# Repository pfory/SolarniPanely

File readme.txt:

Odkazy
http://pavelrichter.net/category/projekty/fotovoltaika/
http://blog.chupasweb.net/archives/494
https://www.youtube.com/watch?v=ouLa4Ftu3O8¨

Popis
Solární panel z jednotlivých solárních článků. Ukládání přebytečné energie do baterie, použít autobaterii, později nahradit něčím lepším. Vyrobenou energii měnit na 230V a napájet spotřebiče

Co potřebuji
- solání články + kabely, ebay 5x5" 125x125mm, 2,7W/článek nominální napětí 0,55 - 0,6V/článek 
https://www.ebay.com/itm/2-8W-125MM-Monocrystalline-Solar-Cells-5x5-A-Grade-For-DIY-Solar-Panels/113344175030?hash=item1a63d6dbb6:m:m1efJgrAq3WPJkaR0fac6-Q:rk:6:pf:0
https://www.ebay.com/itm/40Pcs-125MM-Monocrystalline-Silicon-Solar-Cells-For-DIY-Solar-Panels/302911830537?hash=item4686f3ba09:g:skYAAOSw8hhan8Zm
kolektor 100Wp cca 36ks 9*4 napětí 18V, proud 5,5A 		50ks cena cca 1383,- 
36 článků 996,-

4*125+3*10 =500+30  =530mm   +2*10  +2*19    = 530+20+38 =588mm     590   

9*125+8*1 =1125+8 =1133    +2*10    +2*19    = 1133+20+38=1191mm    1190
                    články  mezera rámeček

rámeček alu profil U 40x25x3 90/m
125+125+62+62=3,75m = 337,-

profil na 2 panely 987 + 140 doprava = 1127
1 panel 560,-

rám 670x1250
sklo 670-2x10=650
1250-2x10=1230

profil pro uchycení na střechu - https://www.ehlinik.cz/al-profil-solar-40x40/pro-2EV0000101.html
délka 2x67 + 2x67 = 4x67 = 268 + mezery 3x2 + kraje 2x5 = 268 + 16 = 284

pro 4 panely zapojené paralelně:
napětí 18V
proud 5,5*4=22A  měl by stačit vodič o průřezu 2,5
výkon 4x100Wp=400Wp

- alu profil https://www.alupa.cz/hlinik/hlinikovy-u-profil-nepr-11x25x13x18/pro-2YS0000101.html 225,-
- sklo 690/m2 panel cca 1m2 - 690,-
- silikon
- regulátor	400,- https://www.ebay.co.uk/itm/10-50A-12-24V-PWM-LCD-Automatic-Solar-Panel-Charger-Controller-Battery-Regulator/122717669692?_trkparms=aid%3D555018%26algo%3DPL.SIM%26ao%3D1%26asc%3D20140122125356%26meid%3Da21eef7c86044d88986fb21765aa5a55%26pid%3D100005%26rk%3D2%26rkt%3D12%26mehot%3Dpp%26sd%3D302957473646%26itm%3D122717669692&_trksid=p2047675.c100005.m1851
- baterie	autobaterie
- měnič 230V
- kabely
- diody
- konektory
- cín
- lepicí páska
- štětec
- nůžky
- ....

Nářadí
- pájka
- svěrák
- pila
- pilník
- šroubovák
- kladivo
- kleště
- klíče

Jeden 100W kolektor by měl za rok vyrobit 80kWh tj. při ceně 6Kč/kWh je cca 480,- za rok

Cenu kolektoru
články 996,-
sklo 782,-
alu profil 350,-
silikon 70,-
tištěné díly + šrouby 50,-

celkem 2248,-

Eko verze s EVA
články 780,-
alu profil 30x20x2 50,7 bez DPH - 3m = 184,-
alu profil 40x20x2 55,9         - 3m = 203,-
doprava 140,-
sklo 4mm cca 115x55 = 380,-
EVA 1000x500*0,4 1m 181,- = 362,-

celkem 780+200+400+362=1742,-

- regulátor 460,-

profil 40x25x3 - 1250
profil 40x25x3 - 620

1.panel
sklo 4mm 65*123
sklo 3mm 65*123
celkem 782,-

2.panel
sklo 4mm 
sklo 3mm 
celkem 782,-

ROZVOD
ze střechy kabelem 4mm do dílny
v dílně baterie, měnič, regulátor a UPS
230 z měniče přes spínací relé do rozvodu UPS
12V přes spínací relé do stávajícího rozvodu 12V

později
dokoupit panely 1 x 115Wp

první panel na střeše jaro 2019
druhý panel na střeše od 16.7.2019
třetí panel - koupeno 15.8.2019 cena 2490,- neosolar.cz na střeše od 20.8.2019

baterie + svorky - koupena 9.9.2019 1197,-

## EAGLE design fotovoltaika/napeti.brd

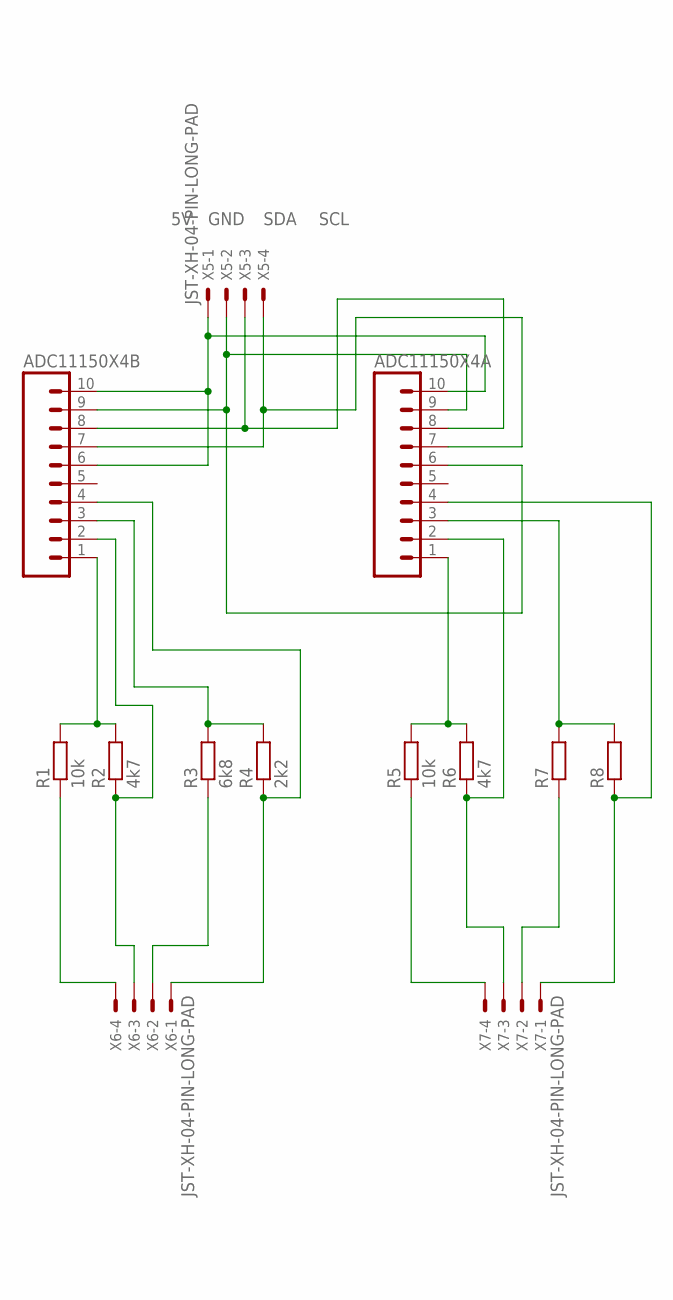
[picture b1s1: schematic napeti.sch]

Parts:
ADC11150X4A, ADC11150X4B: M10; 10P
R1, R5: 10k; 0204/7
R2, R6: 4k7; 0204/7
R3: 6k8; 0204/7
R4: 2k2; 0204/7
R7, R8: R-EU_0204/7; 0204/7
X5, X6, X7: JST-XH-04-PIN-LONG-PAD; JST-XH-04-PACKAGE-LONG-PAD

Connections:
5V: ADC11150X4A.10, ADC11150X4B.6, ADC11150X4B.10, X5.1
GND: ADC11150X4A.6, ADC11150X4A.9, ADC11150X4B.9, X5.2
unnamed: ADC11150X4A.1, R5.2, R6.2
unnamed: R1.1, X6.4
unnamed: ADC11150X4A.2, R6.1, X7.3
unnamed: ADC11150X4A.3, R7.2, R8.2
unnamed: R3.1, X6.2
unnamed: ADC11150X4A.4, R8.1, X7.1
unnamed: R5.1, X7.4
unnamed: R7.1, X7.2
unnamed: ADC11150X4B.1, R1.2, R2.2
unnamed: ADC11150X4B.2, R2.1, X6.3
unnamed: ADC11150X4B.3, R3.2, R4.2
unnamed: ADC11150X4B.4, R4.1, X6.1
SCL: ADC11150X4A.7, ADC11150X4B.7, X5.4
SDA: ADC11150X4A.8, ADC11150X4B.8, X5.3

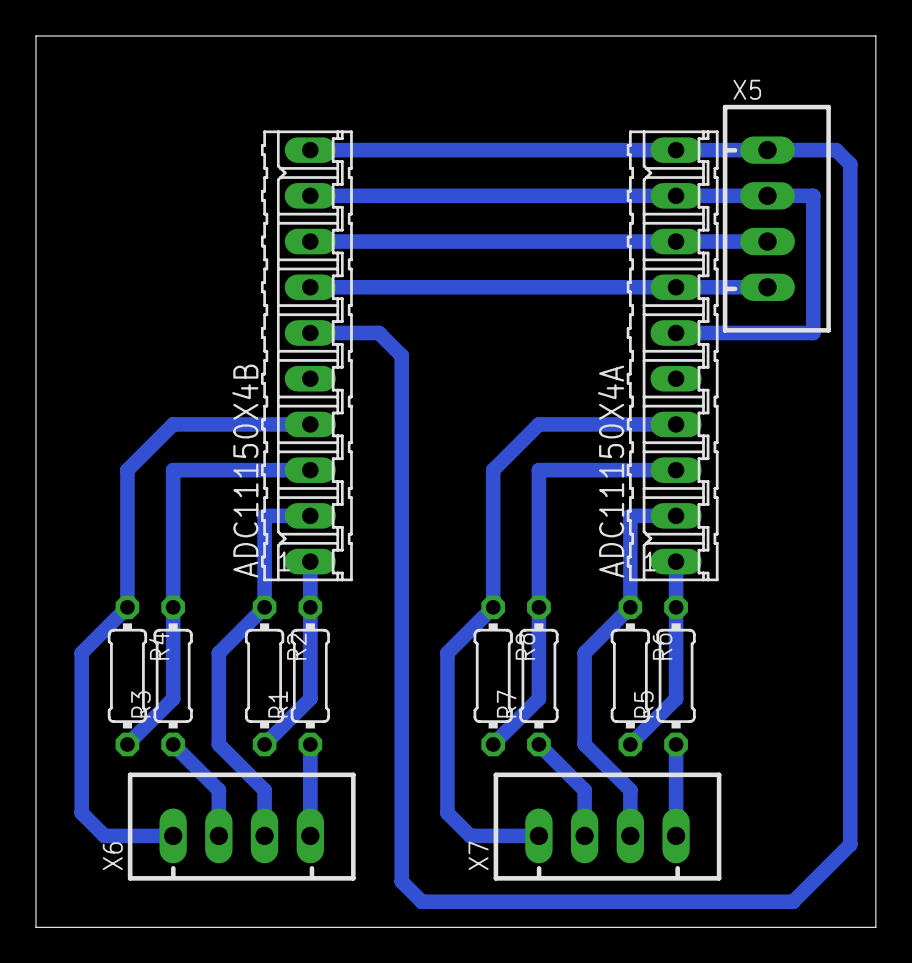
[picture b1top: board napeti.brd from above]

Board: 2 copper layers, 46.7 x 49.5 mm, 13 parts (0 on the bottom side), 16 nets.

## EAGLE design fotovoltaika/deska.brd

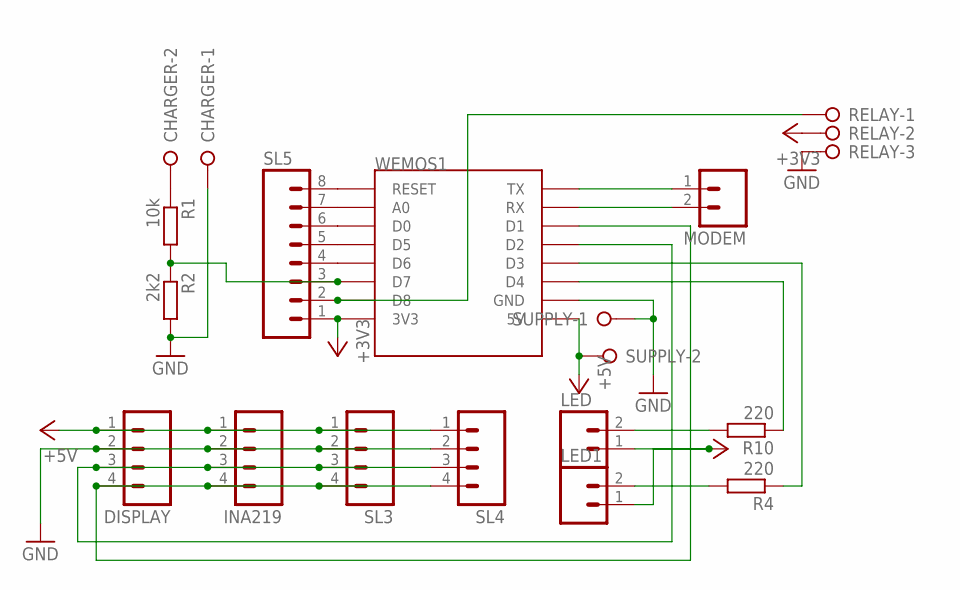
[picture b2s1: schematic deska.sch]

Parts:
CHARGER: W237-02P; W237-132
DISPLAY: M04; 04P
INA219: M04; 04P
LED, LED1: M02; 02P
MODEM: M02; 02P
R1: 10k; 0207/10
R2: 2k2; 0207/10
R4, R10: 220; 0207/10
RELAY: W237-3E
SL3, SL4: M04; 04P
SL5: M08; 08P
SUPPLY: W237-02P; W237-132
WEMOS1: WEMOS-D1-MINI

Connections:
+3V3: RELAY.2, SL5.1, WEMOS1.3V3
+5V: DISPLAY.1, INA219.1, LED.1, LED1.1, SL3.1, SL4.1, SUPPLY.2, WEMOS1.5V
GND: CHARGER.1, DISPLAY.2, INA219.2, R2.2, RELAY.3, SL3.2, SL4.2, SUPPLY.1, WEMOS1.GND
unnamed: DISPLAY.4, INA219.4, SL3.4, SL4.4, WEMOS1.D1
unnamed: DISPLAY.3, INA219.3, SL3.3, SL4.3, WEMOS1.D2
unnamed: SL5.7, WEMOS1.A0
unnamed: RELAY.1, SL5.2, WEMOS1.D8
unnamed: CHARGER.2, R1.1
unnamed: SL5.4, WEMOS1.D6
unnamed: SL5.5, WEMOS1.D5
unnamed: SL5.6, WEMOS1.D0
unnamed: R1.2, R2.1, SL5.3, WEMOS1.D7
unnamed: R10.1, WEMOS1.D4
unnamed: LED.2, R10.2
unnamed: SL5.8, WEMOS1.RESET
unnamed: MODEM.1, WEMOS1.TX
unnamed: MODEM.2, WEMOS1.RX
unnamed: LED1.2, R4.2
unnamed: R4.1, WEMOS1.D3

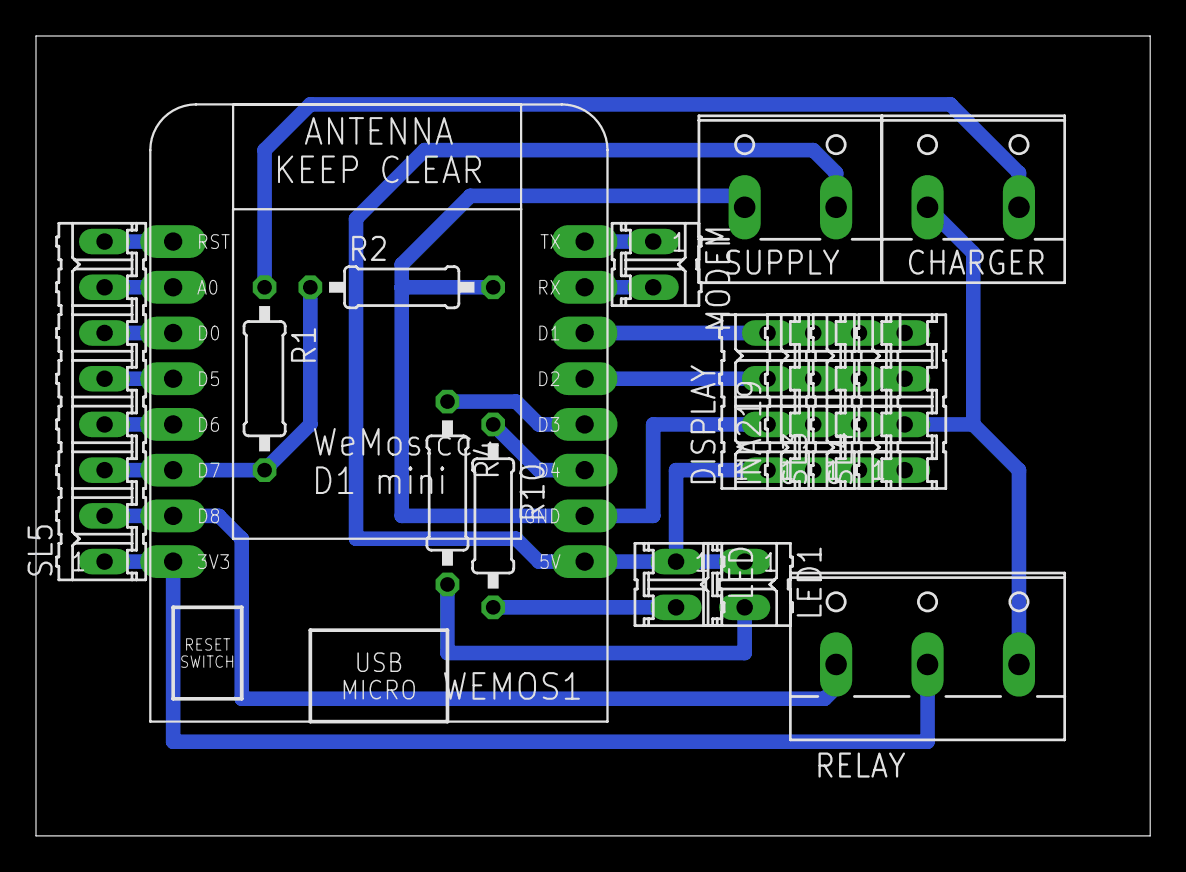
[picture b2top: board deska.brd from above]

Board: 2 copper layers, 61.9 x 44.4 mm, 16 parts (0 on the bottom side), 19 nets.

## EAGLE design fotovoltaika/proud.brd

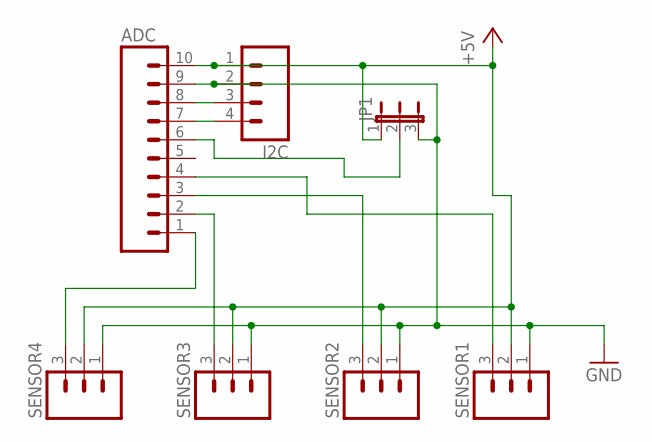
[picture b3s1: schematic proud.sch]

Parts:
ADC: M10; 10P
I2C: M04; 04P
JP1: JP2E; JP2
SENSOR1, SENSOR2, SENSOR3, SENSOR4: M03; 03P

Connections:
+5V: ADC.10, I2C.1, JP1.1, SENSOR1.2, SENSOR2.2, SENSOR3.2, SENSOR4.2
GND: ADC.9, I2C.2, JP1.3, SENSOR1.1, SENSOR2.1, SENSOR3.1, SENSOR4.1
unnamed: ADC.1, SENSOR4.3
unnamed: ADC.8, I2C.3
unnamed: ADC.2, SENSOR3.3
unnamed: ADC.3, SENSOR2.3
unnamed: ADC.4, SENSOR1.3
unnamed: ADC.7, I2C.4
unnamed: ADC.6, JP1.2

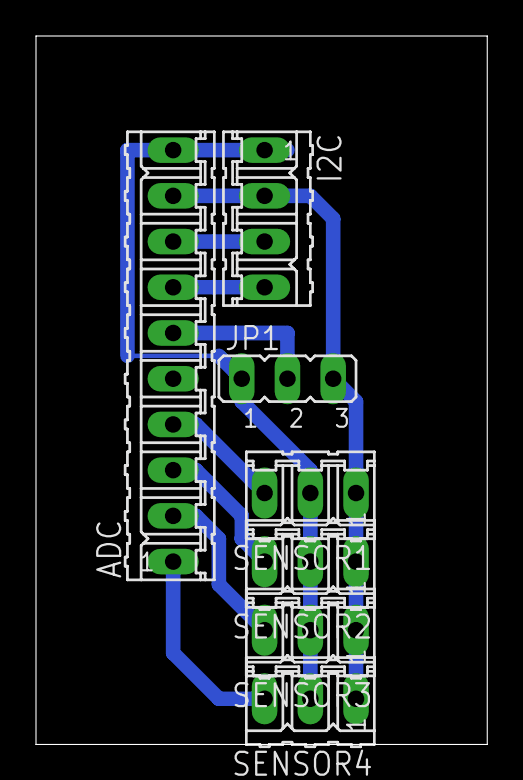
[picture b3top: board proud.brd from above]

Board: 2 copper layers, 25.1 x 39.4 mm, 7 parts (0 on the bottom side), 9 nets.

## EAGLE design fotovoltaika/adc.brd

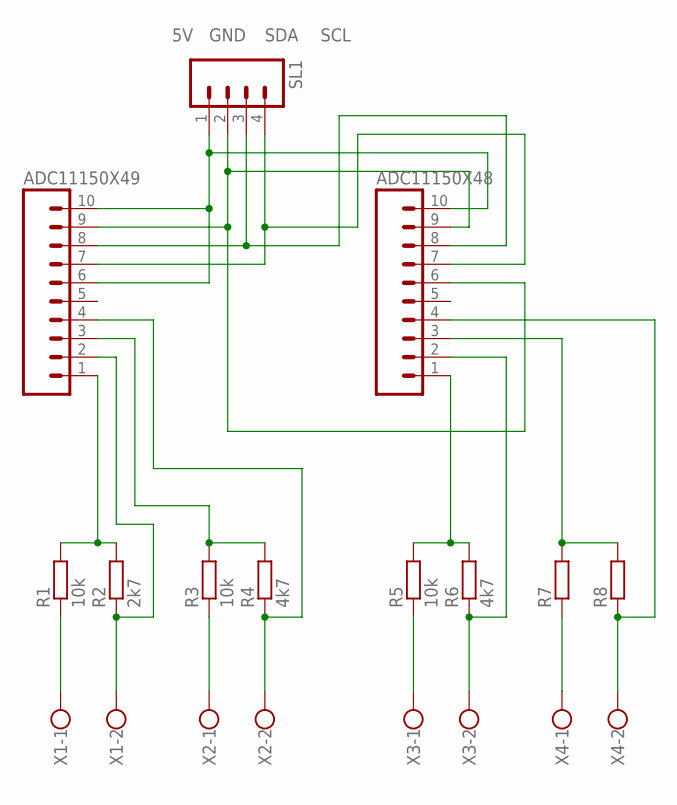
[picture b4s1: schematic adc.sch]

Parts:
ADC11150X48, ADC11150X49: M10; 10P
R1, R3, R5: 10k; 0204/7
R2: 2k7; 0204/7
R4, R6: 4k7; 0204/7
R7, R8: R-EU_0204/7; 0204/7
SL1: M04; 04P
X1, X2, X3, X4: W237-102

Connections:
5V: ADC11150X48.10, ADC11150X49.6, ADC11150X49.10, SL1.1
GND: ADC11150X48.6, ADC11150X48.9, ADC11150X49.9, SL1.2
unnamed: ADC11150X48.1, R5.2, R6.2
unnamed: R1.1, X1.1
unnamed: ADC11150X48.2, R6.1, X3.2
unnamed: ADC11150X48.3, R7.2, R8.2
unnamed: R3.1, X2.1
unnamed: ADC11150X48.4, R8.1, X4.2
unnamed: R5.1, X3.1
unnamed: R7.1, X4.1
unnamed: ADC11150X49.1, R1.2, R2.2
unnamed: ADC11150X49.2, R2.1, X1.2
unnamed: ADC11150X49.3, R3.2, R4.2
unnamed: ADC11150X49.4, R4.1, X2.2
SCL: ADC11150X48.7, ADC11150X49.7, SL1.4
SDA: ADC11150X48.8, ADC11150X49.8, SL1.3

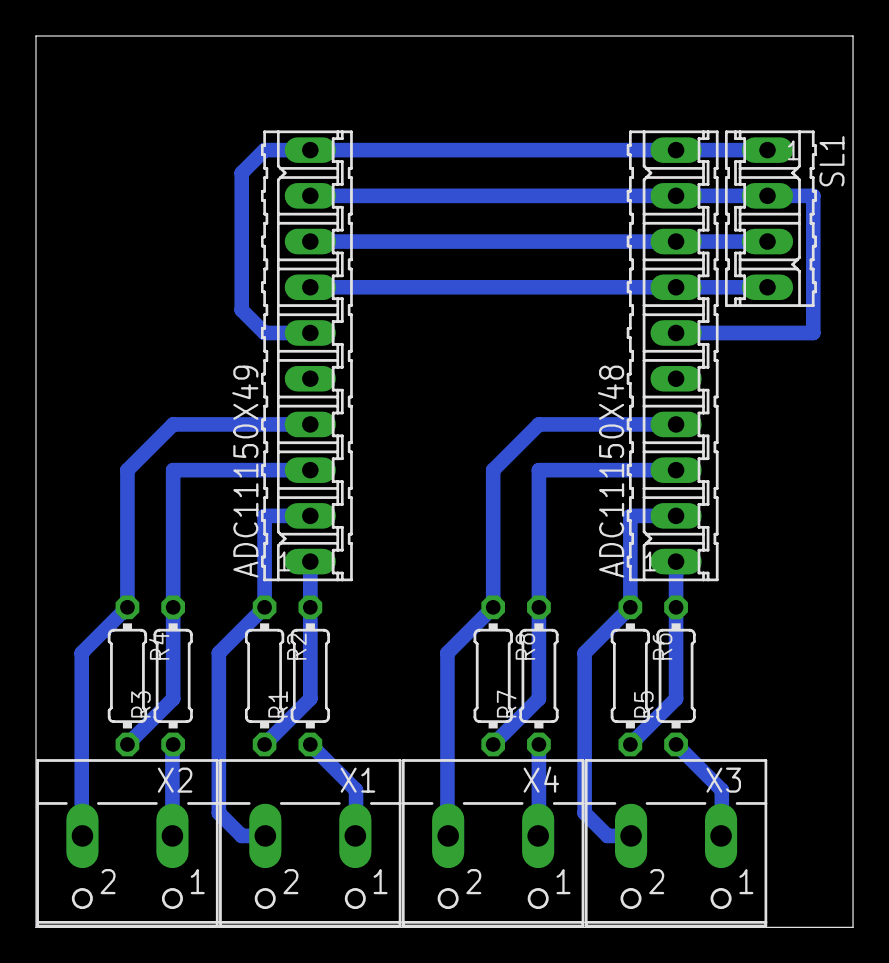
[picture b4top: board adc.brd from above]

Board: 2 copper layers, 45.4 x 49.5 mm, 15 parts (0 on the bottom side), 16 nets.

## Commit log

2018-12-07 popis
2018-12-12 + cidlo proudu
2019-02-18 aktualizace cen
2019-03-27 + proudovy meric s ACS758
2019-04-02 monitor vystupu regulatoru
2019-04-03 zmena nazvu +ota
2019-04-04 drobne zmeny
2019-04-05 pridana kalkulace eko verze panelu
2019-05-01 zmena napeti
2019-05-02 +ads1015
2019-05-03 - cteni napeti z ad prevodniku
2019-05-10 + schema ADC
2019-05-17 oprava statusu
2019-05-21 upravy desek
2019-05-23 interval posilani dat 5sec
2019-05-29 + mereni interniho napeti chipu a odesilani na HA
2019-06-10 +INA
2019-07-08 uprava desky ovladani rele
2019-07-08 uprava desky
2019-07-11 - upravy kodu
2019-07-12 + pir
2019-07-17 doplnění popisu
2019-07-17 zmena odporu delice
2019-08-05 + desky
2019-08-14 + měření výstupu do střídače
2019-08-15 + zmena rozsahu ina 2 na 2A
2019-08-19 + popis odběru
2019-08-21 + displej
2019-08-27 kosmetika
2019-09-02 zobrazovani na displej
2019-09-02 0,40
2019-09-02 + spinani rele
2019-09-02 0.43
2019-09-03 prohozeni intervalu pro on a off, bylo to obracene
2019-09-03 0.48
2019-09-03 0.49
2019-09-04 bez spinani rele
2019-09-04 + ruční spínání relé
2019-09-10 zobrazovani na displeji
2019-09-10 0.60
2019-09-10 + manual
2019-09-15 voltage to 12V
2019-09-16 prodloužení intervalu sepnutí relé na 1 hodinu dělení proudu 2, nevím proč vychází proud 2x více než ve skutečnosti je, zjistit
2019-09-16 pokud neni sepnuto rele tak je vystupni vykon 0
2019-09-16 zobrazeni minut zbyvajicich k sepnuti rele
2019-09-16 zmena na spinani a rozepinani podle napeti vystupu outpin ma jiz jen informativni charakter
2019-09-17 + schema
2019-09-17 +druhe rele
2019-09-20 zmena urovni nabiti a vybiti baterie zmena rozliseni vystupniho merice napeti
2019-09-22 měření napětí prohození INA na výstup vstup konstantně 12V
2019-09-23 spínání při nastaveném vstupním proudu z panelu při startu nastavit relé na OFF
2019-09-24 oprava stavu ledky po startu
2019-09-25 +tepolota
2019-09-25 +zobrazeni min a ah na displeji + vypocet
2019-09-26 formátování výstupů na lcd
2019-09-26 vyčištění kódu od zbytečností
2019-09-26 +datasheet
2019-10-01 ota zapnuti
2019-10-01 nove zobrazeni cisel na displeji
2019-10-03 oprava chyb
2019-10-03 stav rele
2019-10-03 oprava pozice na displeji
2019-10-04 pir bez interruptu
2019-10-07 nulovani displeje
2019-10-08 zobrazeni statistik na displeji
2019-10-10 upravy kodu
2019-10-10 uprava desky pro mereni napeti pro JST-XH konektor
2019-10-10 zmena na konektory JST-XH
2019-10-28 zmena delicu
2019-10-29 0.83
2019-10-30 prepocet napeti vstupu a vystupu
2019-10-30 zmena usporadani displeje
2019-10-30 posilani spinacich napeti MQTT
2019-10-31 komentare napeti pro spinani a rozpinani rele
2019-10-31 uprava spinani rele
2019-11-01 - defaulty pro napeti na 121V - uprava aby se neposilali spatne hodnoty napeti
2019-11-05 prodleva mezi 1-0 a 0-1 na 60 sec v 0.85
2019-11-10 auto pri startu
2019-11-10 0.86
2019-11-12 oprava chyby pri ukladani hodnot ONVoltageSmall a big
2019-11-17 patch na neustale zasilani zprav manualRelay
2019-11-25 0.88 + zobrazeni ocekavaneho vykonu na displeji
2019-11-26 oprava zobrazeni textu na displeji
2019-11-26 displej
2019-11-27 spravne zobrazovani FP
2019-11-28 - vypnuti rele pokud na nasledujici den neni dobra predpoved
2019-12-02 0.92 prodlozeni intervalu mezi rozepnutim rele a opetovnym sepnutim na 10 minut
2019-12-03 0.93 zmena limitu pro predpoved vykonu na dalsi den
2019-12-03 odeslani stavu rele pri rucnim ovladani
2019-12-05 + vytezovac
2019-12-05 0.02 zmena topicu
2019-12-06 posilani statusu
2019-12-06 + ota
2019-12-06 zmena topicu
2019-12-06 opravena chyba pri manualnim prepinani
2019-12-25 posilani rssi jednou za 10 minut kvuli tomu, ze to dlouho trva
2020-02-13 uprava podminek pro spinani rele
2020-02-13 uprava podminek pro spinani/rozpinani rele zavedeni stavu zmeny rele
2020-02-13 + duvod zmeny pri ustalenem stavu= 0
2020-02-14 update sender
2020-02-19 zmena delay na 2minuty
2020-03-26 zmena topicu pro rele
2020-04-20 zmena proudu na 6A
2020-05-07 změna limitu 2A-4A
2020-05-12 + podminka na vypnuti kdyz odber je vetsi nez prikon
2020-07-23 v 1.00 - opraveny stavy rele
2020-08-05 zmena 6 odtsranena
2020-08-05 include do configu
2020-08-05 1.02 add doubleresetdetector
2020-09-17 funkcni Doublereset detector
2021-03-17 + powerMeter
2021-04-19 vypinani displeje 22-06
2021-04-20 oprava chyby zhasinani displeje
2021-11-30 + config portal
2021-12-07 0.30
2022-03-09 uprava zobrazeni + teplota bojler + watty vstup a vystup
2022-03-11 oprava vypoctu vystupni energie
2022-03-24 zmena mqtt pro vytezovac
2022-06-14 uprava topicu pro vytezovac
2023-03-15 uprava mqtt sablony
2024-02-04 lokalni time server
2024-04-08 uprava kvuli zamene spinače
